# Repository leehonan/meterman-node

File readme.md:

# Meterman MeterNode

This repo contains PCB designs and firmware for a low-cost, low-power, wireless LED pulse meter node.  It was designed to read and transmit energy consumption from an electricity smart meter LED pulses, but could be used for other LED pulse counting applications.  

This 'MeterNode' is part of a basic electricity monitoring system described at http://leehonan.com/meterman.  The 'MeterMan' system consists of:

* One or more MeterNodes, transmitting energy consumption at set intervals using sub-GHz packet radio (RFM69 @ 434/868/915MHz).

* A [Gateway](https://github.com/leehonan/rfm69-pi-gateway), being a Raspberry Pi 'Hat' that bridges the RFM69 network to a Raspberry Pi's UART Serial interface.

* A [Server](https://github.com/leehonan/meterman-server) that runs on the Pi, maintains energy consumption data, and provides access to this and other operational data through an API, a file journal, and a realtime socket API (socket API is TBD).

## This Repo

This (MeterNode) repo consists of:

* The MeterNode PCB design (authored in KiCad).  This mounts in a small 3D-printed box and is powered by 3xAA Batteries or a DC adapter.  It attaches to a small 'puck' sensor using a 3.5mm audio cable.

* The MeterNode Puck PCB design (also KiCad).

* 3D shape files (.STL) for the puck housing.

* Source code for the MeterNode firmware (AVR C with Arduino extensions).  

All contents are licenced according to the MIT licence.

## MeterNode Overview
The image below shows a partially-populated MeterNode installed in a project box with a 3xAA battery holder (empty space at bottom left due to omitting CT and DC power sub-circuits).

The MeterNode's companion 'Puck' is a peripheral pulse sensor (not really in the shape of a puck - although that was the original idea).  It has a photoresistor on one side, and a red 'super bright' LED on the other.  The photoresistor is placed over the smart meter's 'consumption' LED, and connected to the monitoring MeterNode using a TRS or TRRS 3.5mm cable (with a 3.5mm TRRS jack on each PCB).  

<table><tr>
<td align="center">

</td>
<td align="center">

</td>
</tr></table>

The smart meter's consumption LED will pulse on/off as a particular unit of power is consumed (e.g. 1 pulse per watt-hour/Wh) - this varies by meter and is configurable on the MeterNode.  The puck's red LED can flash in unison with the smart meter (off by default to conserve battery).

While there are a number of ways to interrogate a smart meter (e.g. ZigBee, Serial and Optical ports), the approach used is cheap, non-invasive, hacker-friendly, and 'permissionless'.  Zigbee is not cheap, not hacker-friendly, and requires multiple permissions (including a Zigbee production cert and utility device authorisation).  Optical ports vary by meter and are usually password-protected.  Many meters do not have serial ports.

Later iterations may include direct wired metering ('behind' the smart meter) and additional CT clamps.

The MeterNode itself comprises:
* A DC power sub-circuit, switchable between battery/DC jack (3VDC to 5VDC) and FTDI (or off if no FTDI connection).  Uses a MCP1700 regulator to supply 3.3VDC.  Includes an upstream voltage divider for reading VIN or battery voltage (giving an indication of the battery's remaining charge).

* An ATMega 328P MCU sub-circuit, along the lines of common 'minimal low-power Arduino' circuits.  FTDI Header for programming and control.

* A PCF2123 low-power RTC.

* A radio sub-circuit with an RFM69W module.  The design uses an RP-SMA connector, but the PCB also supports uFL or a wire antenna.

* A sub-circuit to integrate the Puck, with a nano-comparator to give a definitive low/high signal to the MCU.  Because this is a slow-moving signal a Schmitt Trigger is used to avoid oscillation (through hysteresis).

* A sub-circuit to integrate a CT clamp, as used by [OpenEnergyMonitor's emonTX](https://github.com/openenergymonitor/emontx3).  This may be left unpopulated and is probably not practical to use if mounting next to a smart meter which tends to be outside and some distance from the distribution board/panel, which is typically indoors (unless running a long cable to the Puck).

The following images show a fully-populated MeterNode, with a DC jack and CT Clamp, alongside a partially-populated MeterNode with neither.

<table><tr>
<td align="center">

</td>
<td align="center">

</td>
</tr></table>

## Operation

The MeterNode 'sleeps' in normal operation (consuming about 80uA/microamps), with the MCU waking on an interrupt to record each meter LED pulse and send/receive messages as dictated by configurable timers.  

Given that it wakes/sleeps sporadically, the MeterNode initiates all two-way communication with the Gateway.  Configuration/control instructions to the MeterNode are effectively queued at the Gateway and despatched to the MeterNode when it requests 'Gateway Instructions' (GINR message).  While these instructions are usually polled for at a 'lazy' rate (e.g. every ten minutes), an aggressive polling instruction (GITR message) can be sent to cause the MeterNode to temporarily poll more frequently (e.g. every 30s for 5 min).

The Meternode's operation follows a loop:

* Wake up when an interrupt is triggered by an LED pulse. (At boot the Meternode will stay awake for 15s).

* Log the LED pulse with a timestamp from the onboard RTC, flashing the puck LED if configured.

* Check whether the current metering interval has expired (e.g. 30s), and if so, close it and begin a new one in the metering ring buffer (with a current reading from the CT clamp if configured).  Also check whether a 'meter update' message needs to be sent to the gateway.

* Check whether timers have expired for other periodic tasks, such as synchronising the RTC, adjusting Radio TX Power to fit target RSSI, or getting Gateway Instructions.  

* If required, check for an instruction from the gateway (passing status info such as battery voltage in the request) and process it.

* Sleep until the next LED pulse.

### Metering Approach & Limitations

The MeterNode simply counts consumption LED pulses, and records these against interval entries, with timing according to its onboard clock (RTC).  The pickup/counting is 100% accurate if the sensor is setup properly and not subject to extreme light interference.  A cumulative meter value is stored and transmitted in each message, allowing for interval update message failures.

The MeterNode can be set to a notional 'base value' to track the smart meter being monitored.  This allows for easy verification that the MeterNode is tracking accurately, although it is difficult to align the two exactly as the smart meter will only display a coarse value (e.g. to the nearest 100 Wh).  This can be set using a serial command or radio message as described below.

In normal operation, the MeterNode will create/close interval entries every n seconds, and despatch these in 'meter update' messages to provide energy consumption snapshots.

In the unlikely case that the smart meter is dormant (i.e. 0Wh consumption), the MeterNode will sleep ad infinitum, but then wake and send an update message that may have skipped previous intervals.

The MeterNode will execute a 'rebase' any time its clock changes, or the meter's base value is reset.  This results in a 'rebase message' which instructs consumers that the time/energy basis of the accumulation meter has changed.  Rebases will occur when:

* The MeterNode is booted.

* The RTC is set.

* The base value of the accumulation meter is changed.

* The accumulation meter cycles from its maximum value (4.2 GWh) to 0 Wh.  (Note that smart meters themselves are occasionally zeroed/cycled arbitrarily, e.g. by remote firmware upgrades.)

The MeterNode cannot:
* Guarantee a message element for every 0Wh consumption interval, or indeed guarantee that any message will be sent/received successfully.

* Guarantee a rebase message will be received.  Consuming applications should alert on large increases or reversals in time/meter values.

* Maintain meter readings between reboots (that would necessitate constant writing to EEPROM, which degrades after ~100K writes).

* Check itself against the meter being tracked.

* Confirm that it is alive, or detect issues with its sensor (as it will be asleep) - although this can be done at the consuming node(s).

### MeterNode Hardware Interface
The MeterNode PCB has the following switches, buttons, headers, and adjustable components.  These are shown below.
<table><tr>
<td align="center">

</td>
<td align="center">

</td>
</tr></table>

* A VIN switch that toggles between either battery/DC-in or FTDI/Off.  A battery must not be connected at the same time as a DC adapter, but either can be connected at the same time as a FTDI adapter.  If the switch is in the FTDI/Off position but FTDI is not connected the device will be off.  Conversely if the switch is in the battery/DC-in position but a FTDI adapter is connected, power will be drawn from the battery/DC adapter (with other FTDI functions working as normal).

* A MCU Reset button that reboots the MCU.

* An auxiliary button that is used to either toggle sleep mode or enable a temporary alignment mode:

    - If sleeping, any detected press will set sleep off (3 flashes).
    Release as soon as flashing starts.  Will need to hold down until
    interrupt fires (i.e. watched LED pulses).

    - If not sleeping, short press of < 1s will set sleep on (5 flashes).
    Release as soon as flashing starts.

    - If not sleeping, long press of > 3s will start a 60s adjustment mode (7
    flashes) that forces meter LED rate to 1, and time to 0 (mimic watched
    LED).  This will cause the Puck LED to flash in unison with the smart meter's LED for 60s.

* An FTDI header for use with a USB-FTDI adapter.  This is used to upload firmware and also to interact with the MCU directly over a serial connection (viewing events and using the MeterNode's command protocol to view information and change settings).  Firmware can be uploaded using avrdude directly, or via an IDE (such as platform.io).  Depending on the adapter and client software uses, this may reset the MCU.

* A breakout header that is used for setup and diagnosis, typically with a multimeter.  The positions are described below and pictured earlier:

| Position | Description |
| :--- |:---|
| GND | DC Ground. |
| 3V3   | 3.3VDC from regulator.  |
| LDR  | Output from LDR, fed to Comparator via Schmitt Trigger (from which it is segregated by a 1K resistor). <br> Tuned using the LDR trimpot, typically 0.2V to 2.0V (LED on-off). |
| CV+  | V+ input to Comparator, affected by Schmitt trigger feedback. |
| CREF  | LDR Comparator Reference Voltage (ideally 1.5V).  Set using the REF trimpot. |
| COUT | Output from Comparator.  Should be Low (0V) or High(3.3V).  Goes to MCU D3 (interrupt 1). |   
| CT | Output from CT clamp circuit.  Value from 0V to 3.3V is linear representation of RMS current.  Goes to MCU A1.  |

### Puck Setup
The setup and calibration of the light-dependent resistor (LDR) is critical.  It should be positioned directly over the LED being monitored, and shielded from ambient light.  It is best installed using double-sided tape to affix the base of the housing to the smart meter, ensuring that the LED is centred in the base's hole (that the photoresistor 'looks through').  See the assembly instructions below for more detail.

While the approach used is not overly sensitive to ambient light (compared with photodiodes, or an LDR without a comparator and schmitt trigger), minimising ambient light will increase the range around the comparator's reference/trigger point.  In practice the design used can work with some intrusion of relatively bright light (e.g. direct sunlight on a meter), but only up to a point.

With the MeterNode on and the puck installed, connected:
* Connect a multimeter to GND/CREF.  Adjust to 1.5V using the REF trimpot.

* Move the positive probe to the LDR breakout header position.  Adjust the LDR trimpot until you see a substantial swing between low and high states (e.g. 0.2V to 2.0V) around CREF.  A high level of ambient light may boost the lower value.  The trimpot's effective zone if fairly small - it will appear to be stuck high or low for many turns, and then suddenly become responsive.

* Move the positive probe to the COUT breakout header position.  This should be swinging between 0V (low) and 3.3V (high) to indicate reads.

Given that the actual hystersis gap of the comparator circuit is ~10mV, in theory a small swing either side of CREF will be sufficient to produce a definite high/low reading.  However, using a very wide value will compensate for fluctuations in ambient light and other factors.

### CT Clamp Setup
The design and firmware assumes a YHDC SCT-013-000 CT clamp, which has 100A max current.

A 22 Ohm burden resistor is used to output a voltage proportionate to CT clamp's secondary coil voltage.  

This configuration can measure up to 97A (23.3kW @ 240V).  The minimum reliable detection current is 0.3A, with potential for noise below this.  The constant CT_IRMS_HIGH_PASS is used to set a high-pass filter (0.3A by default).

WARNING: Be careful not to unplug the CT clamp from node while it's clamped to a 'live wire'.  It may shock.  There is a protection diode in the clamp, but its protection shouldn't be relied upon.

### Uploading Firmware
Firmware is uploaded using avrdude (alternately through an IDE such as atom/platform.io, the Arduino IDE may work too).  For an FTDI adapter with Id A403JXEV on OSX or Linux the command will be something like (change device and path to firmware):

```
sudo avrdude -c arduino -p atmega328p -P /dev/cu.usbserial-A403JXEV -b 115200 -U flash:w:/home/tmp/firmware.hex
```

### Serial Communication & Console
A serial connection can be made using a baud of 115200bps, 8N1 (8 data bits, no parity bit, 1 stop bit).  E.g. with minicom and a FTDI adapter at /dev/cu.usbserial-A403JXEV:

```
sudo minicom -b 115200 -o -D /dev/cu.usbserial-A403JXEV
```

Note that connecting or disconnecting a FTDI adapter will not cause a reboot when running on battery power.

The following commands are available through the serial console (case-insensitive):

| Command | Description |
| :--- |:---|
| help | Prints a list of commands. |
| z  | Toggles sleep on and off. |
| ctcl | Toggles CT Clamp on and off. |
| dump  | Prints (dumps) MeterNode config and status to the console.  |
| rcfg | Reset Config.  Resets configuration values stored in EEPROM to defaults and re-applies these.  |
| time | Prints current time from RTC. Set using time=[seconds since UNIX epoch, UTC] |
| logl | Prints log level - ERROR, WARN, INFO, DEBUG.  Set with logl=[log level]|
| ekey | Prints encryption key (16 byte AES) used by network participants for radio comms.  Set with ekey=[encryption key], e.g. ekey=CHANGE_THIS_ASAP|
| neti | Prints MeterNode's Network Id comprised of octets akin to an IP address but with an extra subnet (as the 4 octets define a subnet, with node addressing within this).  Set with neti=[network_id].  At least two octets need to be non-zero so 0.0.1.1 is the 'lowest' usable network subnet.  E.g. neti=0.0.1.1|
| gwid | Prints the 'node id' for the gateway.  This should be 1 by convention, but can be any unallocated address from 1 to 253. Set with gwid=[gateway Id]|
| noid | Print/set MeterNode's node id (set with noid=[node id]).  2-253 by convention. |
| trss | Print/set target RSSI for auto-tuning (set with TRSS=[target RSSI]).  Range is -100 (no signal) to 1 (almost no noise), 0 is disable auto-tuning. -75 is a reasonable value. |
| txpw | Print/set transmission power (set with TXPW=[tx power in dBi]).  For RFM69W range is -18 to +13, for RFM69HW is -14 to +20. Higher values will use more power. |
| mtrv | Set meter value (set with MTRV=[meter value]) in Wh.  May be used to track electricity meter's register. Will overflow and cycle to 0 at 4.2 billion Wh. |
| mtrr |  Print/set meter impulse per kWh rate (set with MTRR=[impulse count]).  E.g. mtrr=1000. |
| mtri |  Print/set meter interval (set with MTRI=[meter interval in sec]).  Up to 255. |
| test |  Toggle test mode, forcing sleep off and simulating watched meter LED pulses. |
| ledr |  Print/set puck LED rate (set with LEDR=[rate per meter LED]).  This is the number of 'watched meter' LED flash/pulses per 'puck' LED flash in response.  E.g. could flash once every 10 to consume battery.  0 means LED is disabled (except to indicate boot). |
| ledt |  Print/set puck LED time (set with LEDT=[time in millis]).  Is max duration of each LED pulse emitted by the puck in millis. Setting to 0 will cause to flash in unison with meter.  Maximum of 3000, but puck LED will always go low/off on falling edge of meter's pulse. |

###  Radio Protocol
The MeterNode uses the [RadioHead Library](http://www.airspayce.com/mikem/arduino/RadioHead/), and 'Reliable Datagrams' for all messaging.

Messages are AES-128 encrypted, with a maximum payload of 61 bytes.  Fields are comma-delimited, records semi-colon-delimited (only used for meter updates).

In addition to being encrypted, messages are contained within the 'subnet' created by the Network Id setting (e.g. 0.0.1.1), with each node having an identifier between 1 and 254 (255 is broadcast).  By convention I use 1 for a gateway, with nodes beginning at 2 (e.g. 0.0.1.1.2).

All datetimes are seconds since UNIX epoch (01/01/1970 00:00:00 UTC).

| Message | From | To | Description|
| :--- |:---| :--- |:---|
| Meter Update - with Current | node | gateway | Communicates the _n_ most recent closed meter intervals to the Gateway, with the meter's previous accumulated value (e.g. 100,000Wh), consumption in each interval (e.g. 15Wh), and an 'on the spot' current measurement taken at the end of the interval. <br> Format: `MUPC,<last_entry_finish_time>,<last_entry_meter_value>,{2..n of <interval_duration>,<interval_value>,<spot_rms_current>}` <br> Where in this case meter and interval values are in Wh (configurable) - with last entry value being a baseline accumulation entry (the last entry broadcast by the MeterNode) and interval values being increments to that, interval duration in seconds, current in Amps. <br> E.g.: `MUPC,1496842913428,18829393;15,1,10.2;15,5,10.7`  <br> Due to message size constraints this will contain no more than 2 interval entries.|
| Meter Update - no Current | node | gateway | As above, but without current measurements. <br> Format: `MUP_,<last_entry_finish_time>,<last_entry_meter_value>,{2..n of <interval_duration>,<interval_value>}` <br> E.g.: `MUP_,1496842913428,18829393;15,1;15,5;15,2;16,3` <br> The number of interval entries in each message can be set by a firmware constant, with 3 or 4 being a reasonable value.|
| Meter Rebase  | node  | gateway  | Sent at boot or whenever meter value or RTC adjusted to notify the gateway of step-changes in time or meter value.  'Re-baselines' the meter, such that all prior messages should be regarded as nominal/unreliable for determining an accumulation value.    <br>Format: `MREB,<meter_time_start>,<meter_value_start>` <br> E.g.: `MREB,1496842913428,18829393`|
| Gateway Instruction Request  | node  | gateway  | Instruction Request to Gateway, including node status data. <br>Format: `GINR,<battery_voltage>,<uptime_secs>,<sleeptime_secs>,<free_ram>,<last_rssi>,<puck_led_rate>,<puck_led_time>,<meter_interval_time>,<meter_imp_per_kwh>`<br>E.g.:`GINR,4300,890000,555000,880,-80,10,100,5,1000` |
| Meter Instruction - Set Interval  | gateway  | node | Set accumulation meter interval. Note all such messages from the Gateway inform the node of the last RSSI for that node at the gateway (for use in TX Power auto-tuning).  <br>Format: `MINI,<new_interval>,<last_node_rssi>`<br>E.g.:`MINI,5,-70`  |
| Meter Instruction - Set Temporary Polling  | gateway  | node | Request from Gateway to temporarily increase GINR polling rate for a specified duration (secs). <br>Format: `GITR,<new_rate>,<duration>,<last_node_rssi>`<br>E.g.:`GITR,30,600,-70` |
| Meter Instruction - Set Value  | gateway  | node | Set accumulation meter value. <br>Format: `MVAI,<new_meter_value>,<last_node_rssi>`<br>E.g.:`MVAI,120000,-70`  |
| Meter Instruction - Set Puck LED  | gateway  | node | Set Puck LED pulse rate and duration. <br>Format: `MPLI,<led_pulse_rate>,<led_pulse_duration>,<last_node_rssi>`<br>E.g.:`MPLI,1,500,-70`  |
| Meter Instruction - 'No Op'  | gateway  | node | 'No op' ACK to GINR, provides RSSI for auto-tuning. <br>Format: `MNOI,<last_node_rssi>`<br>E.g.:`MNOI,-70`  |
| Clock Sync Request | node | gateway  | Clock Sync Ping Request to Gateway. <br>Format: `GMSG,<message>`<br>E.g.:`GMSG,BOOT v2. Flags: EX` |
| Clock Sync Response | gateway  | node | Clock Sync Ping Response from Gateway, used to sync local RTC. <br>Format: `PRSP,<request_time_node>,<current_time_gateway>,<align>,<last_node_rssi>`<br>E.g.:`PRSP;14968429155328,1496842915428,1,-70` |
| General-Purpose Message  | any  | any  | Broadcast to all devices in network.  Used to communicate boot event. <br>Format: `GMSG,<message>`<br>E.g.:`GMSG,BOOT v2. Flags: EX`|

**Interpreting Meter Updates**

The Meter Update Message should be interpreted as follows:
* Times are **inclusive**.  So consumption of 10Wh per 30s interval over 2 minutes from 10AM would be treated as:
    ```
    10:00:00 - 10:00:29 = 10Wh
    10:00:30 - 10:00:59 = 10Wh
    10:01:00 - 10:01:29 = 10Wh
    10:01:30 - 10:01:59 = 10Wh
    ```     

* last_entry_finish_time and last_entry_meter_value is for the last entry in the last MUP communicated by the meter node.  So for the example above, at 10:00:00 the interval entry ending at 09:59:59 was closed, and sent in a MUP with the 3 entries that preceded it.  At 10:00:00, 09:59:59 has just expired with an accumulated meter value of 5622Wh - these will form the baseline for the next MUP.

* Given this example, the next MUP is sent at 10:02:00 will be as follows:

    ```
    MUP_,1511737199,5622;30,10;30,10;30,10;30,10;
    ```

* Of course a MUP could be missed (without a rebase).  The consumer should take account of the baseline value, and not merely store/process the interval entries.    

### Power consumption & battery life
When awake the MCU consumes about 7mA/milliamps, and depending on radio config about 30-50mA for a few milliseconds when transmitting messages.  

In typical use, the MeterNode spends >=99% of its time asleep (affected by meter entry interval lengths).  

3xAA batteries should last 6-12 months with infrequent communication (TBC), although theoretically would last several years if sleeping perpetually, about 1-2 weeks if never sleeping.  A conservative meter interval (e.g. 60s), with 4 entries per message, and a long GINR polling interval (e.g. 600s) is recommended.

The MeterNode will function while battery voltage is >= 2.8V (or 2800mV as reported in GINR messages) - with the 328P MCU being the limiting factor, ideally supplied >=3.3V.  Unfortunately the regulator used (MCP1700) is only a step-down regulator - it cannot step-up lower voltages.  It is otherwise an excellent choice for this application.  Consuming applications should set a battery replacement alert threshold, e.g. 3.0V.

Using the puck LED (which consumes about 1mA) to indicate a meter LED flash will reduce battery life significantly - this should be minimised to testing, e.g. to check alignment (which can be performed more accurately with a multimeter).

## Implementation - MeterNode Firmware
For simplicity, the firmware is implemented as a single C++ program (no header file), although it will need supporting libraries to compile.  There is some redundancy versus the companion gateway firmware - the common components may be moved to a library.  Some Arduino library features are used.

The firmware requires a 328P that has been flashed with Optiboot.  It uses practically all of available program flash memory.  If you are hacking or debugging you'll need to comment out a block of code to make space - e.g. the checkButton() or checkTestMode() methods.

Depending on configuration, about 380 bytes RAM will remain free at runtime (on average, of 2K).  

There are a number of configuration settings at the beginning of the source code.  Particular attention should be paid to the 'Main Config Parameters'.

Note that a version is set in the firmware, and broadcast on boot.

The code is fairly well-documented so isn't covered further here.

## Implementation - PCBs & Cases

The MeterNode PCB measures 60x92mm and is designed to fit a widely-available [100x68x50mm 'project box'](https://www.banggood.com/White-Plastic-Waterproof-Electronic-Case-PCB-Box-100x68x50mm-p-948109.html), shown below.

The MeterNode's companion Puck PCB measures 15x20mm and can be mounted in a 3D-printed case (also in this repo).  The puck can be easily aligned with the meter's consumption LED by adhering the base/case only (positioning its hole directly over the LED) before completing the assembly.

The images below show regular pucks both assembled and disassembled, along with an alternate puck configuration, where the black 'collet' piece shown (.STL included) can be used to position the LDR sensor in tight positions.  The protruding arm is used to adhere the sensor (e.g. using double-sided tape).  The particular meter that necessitated this was the iCredit 500 which has its LED tucked into a tight corner.

<table><tr>
<td align="center">

</td>
<td align="center">

</td>
</tr></table>

The Puck Schematic & PCB is straightforward, so isn't discussed further here - except to mention that care should be taken when soldering as its small size means it can heat up quickly.  

### MeterNode Schematic & PCB

The PCB design minimises the use of SMT components, and uses through-hole instead.  When I originally designed the board I wanted to make it 'hobbyist-friendly' with the only SMT component being the easily-solderable RFM69 and RP-SMA connector.  However in subsequent iterations I added the RTC and comparator, where the best choices were SMT.  This makes the board a hodge-podge, and annoying to make in volume (as I have had to for a few experiments). I may do an SMT-only variant in the future.

Highlights:
* The choice of a photoresistor (LDR) was made after a lot of research and experimentation.  Other projects have concluded that LDRs are too slow, or too affected by ambient light.  I found them to be better in terms of power consumption than alternatives such as photodiodes (about 1/10th), while offering a wide pickup range, and responding 'fast enough' (up to 10Hz).

* A TRRS jack is used for the puck and CT as I had a few hundred of these on-hand.  TRRS cables are unnecessary, TRS can be used.  R1 is not connected on the LDR jack, and R1 and R2 are not connected on the CT jack.
These could be hacked for another application.

* The MCP1700 regulator (3.3V) was chosen due to its low quiescent consumption (1.6uA).  I used a regulator because while the 328P and RTC tolerate VIN ~5.5VDC, the RFM69 has a maximum VIN of only 3.6VDC.  

* A voltage divider (consuming about 1.7uA) is used to measure the voltage input to the regulator - chiefly to allow a basic 'battery meter'.

* Any RFM69W or RFM69HW module will work.  I use the RFM69W because it can be tuned to use less TX power than the RFM69HW.  Given that there is no advantage to mixing radios, I use the RFM69HW on gateways because they are cheaper.

* The RTC used (PCF2123) has low quiescent power consumption (as low as 100nA) and is economical.  It needs a 32.768kHz crystal (7pF, +/- 20 ppm).

* The comparator used (TS881) has low quiescent power consumption (as low as 210nA), is simple to use, and is economical.

* The PCB design also contains a basic AC current sensing circuit for use with an optional CT clamp (around an active or neutral wire).  I used the design from [OpenEnergyMonitor](https://learn.openenergymonitor.org/electricity-monitoring/ct-sensors/how-to-build-an-arduino-energy-monitor-measuring-current-only).  This was a late addition to the design as I wanted to avoid looking at their well-established EmonTx project and see how I went my 'rolling my own'.  When I saw how easy the CT was too add I couldn't resist.  Of course, it will often be impractical to install alongside a smart meter unless running a long cable to the puck (as noted above).

The SMT/SMD components are mostly easy to solder with a decent iron and some flux.  The exception is the PCF2123 RTC, where it is very easy to bridge pins.  I suggest:
* doing SMDs first

* lightly tinning each pad, carefully aligning the IC and soldering a corner pin  

* then applying flux and working your way around

* using a multimeter to test for shorts - via easier to access pads (e.g. for 328P IC)

* inspecting with a loupe or magnifying glass

There are a number of videos on youtube on hand-soldering SMDs.

### Parts List

Includes CT clamp and DC jack.

Approx total is USD$35 (not including labour!).  That assumes you purchase common parts in quantity from Chinese suppliers (e.g. resistors, capacitors).  Otherwise cost will be radically higher.  

| Assembly | Part | Qty | Approx <br>Item Cost<br>(USD) | Comments |
| :--- |:---| :--- |:---|:---|
| Puck | PCB | 1 | $0.50 | E.g. 10 for $5 at PCBWay |
| Puck | Case | 1 | $0.50 | 3D-printed, PLA |
| Puck | LDR | 1 | $0.20 | 5MM Light-Dependent Resistor AKA Photo Resistor.  I use hamamatsu, much cheaper alternatives available. |
| Puck | LED | 1 | $0.02 | Super-bright 5mm, 20mA |
| Puck | TRRS Jack | 1 | $0.05 | PJ320D |
| Puck Cable | 3.5mm TRS or TRRS | 1 | $1.00 | No need to get TRRS |
| CT Clamp | YHDC SCT-013-000 | 1 | $8.50 | 100A version |
| MeterNode | PCB | 1 | $0.50 | E.g. 10 for $5 at PCBWay |
| MeterNode | Case | 1 | $3.50 | From Banggood, cheaper in bulk |
| MeterNode | RP-SMA 3dbi Antenna | 1 | $2.90 | I use higher quality ones via RocketScream, cheaper options available. |
| MeterNode | RP-SMA Connector | 1 | $0.50 |  |
| MeterNode | Battery Holder | 1 | $1.00 | Yet to find with JST connector so solder on cable, or directly to PCB. |
| MeterNode | AA Batteries | 3 | $2.00 | Use best you can afford, e.g. lithium |
| MeterNode | JST-PH connector set | 1 | $0.20 | Can solder wires directly. |
| MeterNode | TRSS Jacks | 2 | $0.05 | PJ320D |
| MeterNode | DC Barrel Jack | 1 | $0.10 | 2.1mm |
| MeterNode | PolyFuse | 1 | $0.20 | 50mA @60V, 5mm spacing |
| MeterNode | MCP1700 Regulator | 1 | $0.50 | 3.3V, TO-92 |
| MeterNode | MCU - ATMEGA 328P | 1 | $1.80 | DIP-28, with holder |
| MeterNode | 16MHz Crystal | 1 | $0.20 | |
| MeterNode | PCF2123 RTC | 1 | $1.20 | TSSOP1 |
| MeterNode | 32.768kHz Crystal | 1 | $0.50 | 7pF, +/- 20 ppm, 3.2x1.5mm SMD |
| MeterNode | RFM69W Module | 1 | $3.00 | SMD |
| MeterNode | TS881 | 1 | $0.65 | SOT-23-5 |
| MeterNode | Resistor - 22 Ohm | 1 | $0.01 | 0.25W |
| MeterNode | Resistor - 1 KOhm | 3 | $0.01 | 0.25W |
| MeterNode | Resistor - 10 KOhm | 6 | $0.01 | 0.25W |
| MeterNode | Resistor - 470 KOhm | 2 | $0.01 | 0.25W |
| MeterNode | Resistor - 1 MOhm | 1 | $0.01 | 0.25W |
| MeterNode | Resistor - 2.7 MOhm | 1 | $0.01 | 0.25W |
| MeterNode | Trimpot - 100 KOhm | 1 | $0.50 | Bourns 3296W knock-off |
| MeterNode | Trimpot - 1 MOhm | 1 | $0.50 | Bourns 3296W knock-off |
| MeterNode | Capacitor - 22 pF | 3 | $0.01 | Ceramic disc |
| MeterNode | Capacitor - 100 nF | 8 | $0.01 | Monolithic, Ceramic |
| MeterNode | Capacitor - 1 uF | 1 | $0.02 | Electrolytic |
| MeterNode | Capacitor - 1 uF | 2 | $0.01 | Monolithic, Ceramic |
| MeterNode | Capacitor - 10 uF | 2 | $0.02 | Electrolytic, 4x7mm |
| MeterNode | Diode - 1N4148 | 2 | $0.01 |  |
| MeterNode | Micro SPST Switch | 1 | $0.15 | 3P |
| MeterNode | 6x6mm pushbutton | 2 | $0.02 |  |
| MeterNode | Pin Header | 1 | $0.02 | 6P, 2.54mm pitch |

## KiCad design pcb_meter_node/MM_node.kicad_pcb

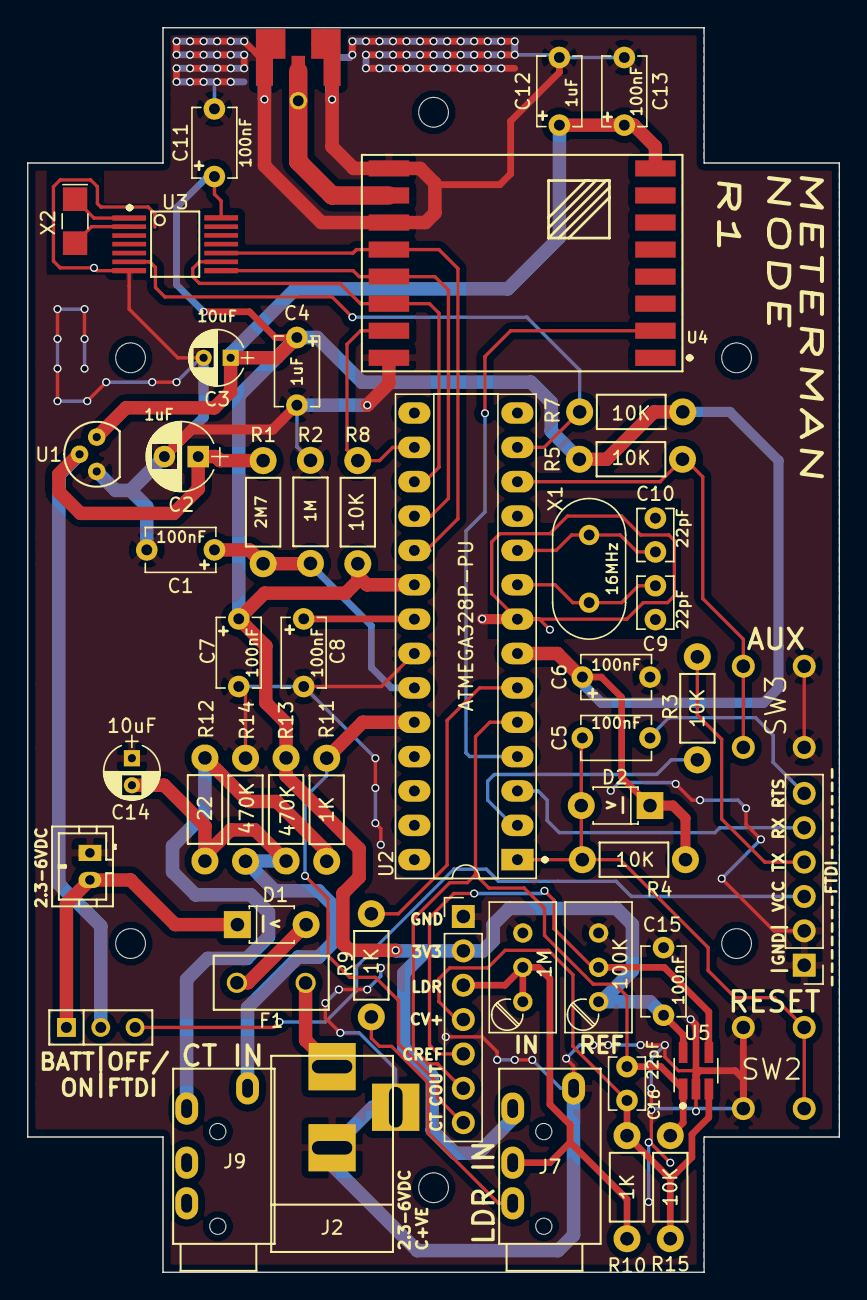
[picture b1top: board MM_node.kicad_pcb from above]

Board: 2 copper layers, 60.0 x 92.0 mm, 60 parts (0 on the bottom side), 35 nets.

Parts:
C1, C5, C6, C7, C8, C11, C13, C15: 100nF; C_Disc_D5.1mm_W3.2mm_P5.00mm
C2: 1uF; CP_Radial_D5.0mm_P2.50mm
C3, C14: 10uF; CP_Radial_D4.0mm_P2.00mm
C4, C12: 1uF; C_Disc_D5.1mm_W3.2mm_P5.00mm
C9, C10, C16: 22pF; C_Disc_D3.8mm_W2.6mm_P2.50mm
D1, D2: 1N4148; D_T-1_P5.08mm_Horizontal
F1: Polyfuse; Fuse_TE5_Littlefuse-395Series
J1: CONN_BATT; JST_PH_B2B-PH-K_02x2.00mm_Straight
J2: CONN_REG; BARREL_JACK
J3: CONN_FTDI; Pin_Header_Straight_1x06_Pitch2.54mm
J4: ANT; Pin_Header_ANT
J5: ANT-UFL; U.FL-R-SMT-LongFeed
J6: ANT-SMA; RF-SMA-EDGE_Without_Feed
J7: CONN_LDR; TRRS_Jack
J9: CONN_CT; TRRS_Jack
J10: CONN_BREAKOUT; Pin_Header_Straight_1x07_Pitch2.54mm
M1, M2, M3, M4, M5, M6: MOUNT_HOLE; HOLE_NPTH_2.2MM
R1: 2M7; Resistor_Horizontal_RM7mm
R2: 1M; Resistor_Horizontal_RM7mm
R3, R4, R5, R7, R8, R15: 10K; Resistor_Horizontal_RM7mm
R9, R10, R11: 1K; Resistor_Horizontal_RM7mm
R12: 22; Resistor_Horizontal_RM7mm
R13, R14: 470K; Resistor_Horizontal_RM7mm
RV1: 100K; Potentiometer_Trimmer_Bourns_3296W
RV2: 1M; Potentiometer_Trimmer_Bourns_3296W
SW1: SW_SPDT; SW_Micro_SPST
SW2: RESET; 6x6mm_pushbutton
SW3: AUX_BTN; 6x6mm_pushbutton
U1: MCP1700-TO92; TO-92_Molded_Narrow
U2: ATMEGA328P-PU; DIP-28_W7.62mm_Socket_LongPads
U3: PCF2123; TSSOP14
U4: RFM69W; RFM69HW_SMD_Handsoldering
U5: TS881; SOT-23-5_HandSoldering
X1: 16MHz; Resonator-2pin_w10.0mm_h5.0mm
X2: 32.168kHz; Crystal_SMD_EuroQuartz_EQ161-2pin_3.2x1.5mm_HandSoldering

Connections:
+3V3: C3.1, C4.1, C6.1, C7.1, C11.2, C12.2, C13.2, C15.1, D2.1, J7.1, J10.2, R4.2, R5.2, R7.2, R8.2, R13.2, RV1.1, U1.3, U2.7, U2.20, U3.14, U4.8, U5.5
/ANT: J4.1, J5.1, U4.10
/BATT_VIN: D1.1, J1.2, SW1.1
/CMP_V+: C16.1, J10.4, R10.1, R15.2, U5.3
/CMP_VREF: J10.5, RV1.2, U5.4
/CONN_CT_SLV: C14.2, J9.4, R12.1, R13.1, R14.2
/CONN_CT_TIP: J9.1, R11.2, R12.2
/CONN_LDR_R1: J7.2, J10.3, R10.2, RV2.1, RV2.2
/CONN_LDR_R2: J7.3, R9.2
/MCU_A1: J10.7, R11.1, U2.24
/MCU_D3_INT1: C16.2, J10.6, R15.1, U2.5, U5.1
/MCU_D4: R9.1, U2.6
/MCU_RESET: C5.1, D2.2, R4.1, SW2.2, U2.1
/MCU_RX: R3.2, U2.2
/MCU_TX: J3.5, U2.3
/MISO: U2.18, U3.8, U4.13
/MOSI: U2.17, U3.9, U4.14
/RAD_INT: U2.4, U4.2
/RAD_SS: R8.1, U2.16, U4.15
/RTC_SS: R7.1, U2.13, U3.6
/RTS: C5.2, J3.6
/SCK: U2.19, U3.10, U4.12
/TXD: J3.4, R3.1
/VIN_REG: C2.1, R1.1, SW1.2, U1.2
/VIN_V_DIV: C1.1, R1.2, R2.1, U2.23
GND: C1.2, C2.2, C3.2, C4.2, C6.2, C7.2, C8.2, C9.1, C10.1, C11.1, C12.1, C13.1, C14.1, C15.2, J1.1, J2.2, J2.3, J3.1, J3.2, J5.2, J5.3, J6.2, J6.3, J6.4, J6.5, J7.4, J10.1, R2.2, R14.1, RV1.3, RV2.3, SW2.1, SW3.2, U1.1, U2.8, U2.22, U3.7, U4.9, U4.11, U4.16, U5.2
unnamed: C8.1, U2.21
unnamed: C9.2, U2.9, X1.1
unnamed: C10.2, U2.10, X1.2
unnamed: D1.2, F1.1
unnamed: F1.2, J2.1
unnamed: R5.1, SW3.1, U2.12
unnamed: U3.1, X2.1
unnamed: U3.2, X2.2
VCC: J3.3, SW1.3

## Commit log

2017-10-16 Create LICENSE
2017-10-18 Baseline Commit from private repo
2017-10-18 no message
2017-12-01 R7, minor doc edits
